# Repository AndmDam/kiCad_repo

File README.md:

# kiCad_repo

Repositorio de mis archivos de mis proyectos de kicad.

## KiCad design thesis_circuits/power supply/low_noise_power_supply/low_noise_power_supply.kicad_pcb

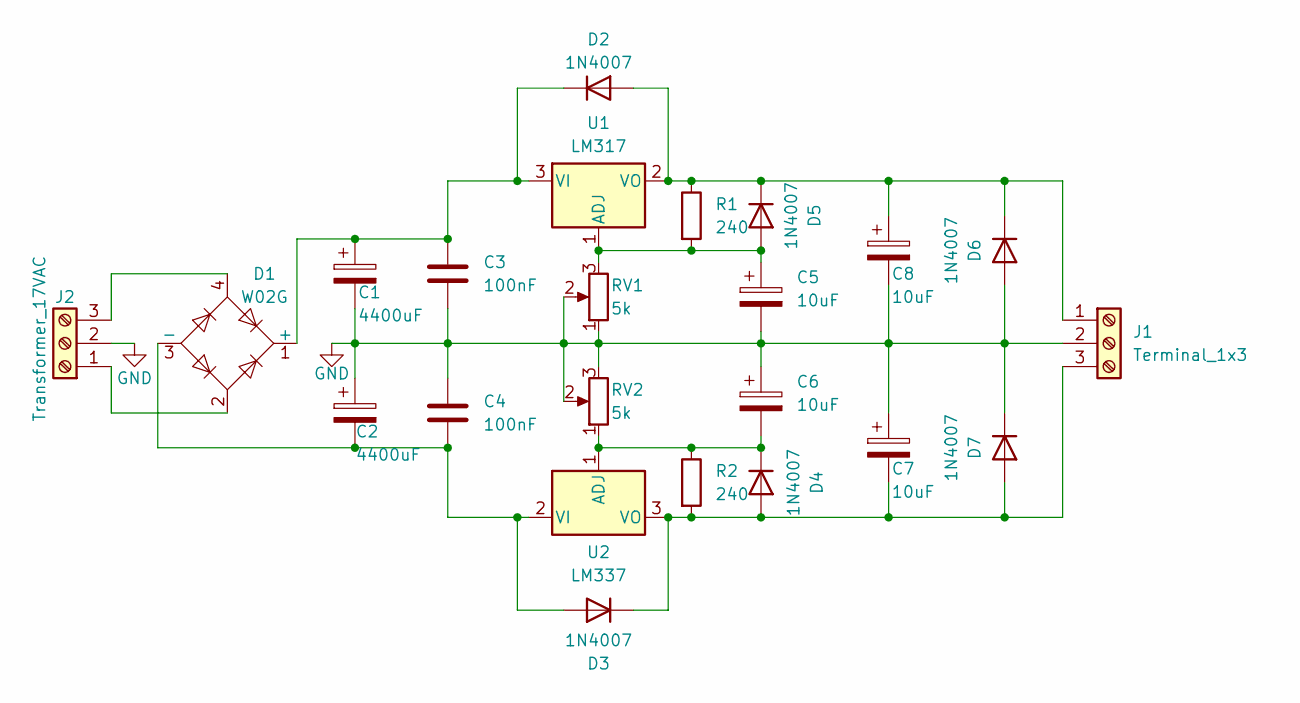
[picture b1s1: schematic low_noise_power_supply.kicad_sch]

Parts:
C1, C2: 4400uF; C_Radial_D18.0mm_H35.5mm_P7.50mm
C3, C4: 100nF; C_Disc_D5.0mm_W2.5mm_P2.50mm
C5, C6, C7, C8: 10uF; CP_Radial_D5.0mm_P2.50mm
D1: W02G; Diode_Bridge_Round_D9.8mm
D2, D3, D4, D5, D6, D7: 1N4007; D_DO-41_SOD81_P10.16mm_Horizontal
J1: Terminal_1x3; PhoenixContact_GMSTBA_2,5_3-G-7,62_1x03_P7.62mm_Horizontal
J2: Transformer_17VAC; PhoenixContact_GMSTBA_2,5_3-G-7,62_1x03_P7.62mm_Horizontal
R1, R2: 240; R_Axial_DIN0204_L3.6mm_D1.6mm_P5.08mm_Horizontal
RV1, RV2: 5k; Potentiometer_Bourns_3299W_Vertical
U1: LM317; TO-220-3_Vertical
U2: LM337; TO-220-3_Vertical

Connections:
GND: C1.2, C2.1, C3.2, C4.1, C5.2, C6.1, C7.1, C8.2, D6.2 (A), D7.1 (K), J1.2, J2.2, RV1.1, RV1.2, RV2.2, RV2.3
unnamed: C1.1, C3.1, D1.1 (+), D2.1 (K), U1.3 (VI)
unnamed: C2.2, C4.2, D1.3 (-), D3.2 (A), U2.2 (VI)
unnamed: C8.1, D2.2 (A), D5.1 (K), D6.1 (K), J1.1, R1.1, U1.2 (VO)
unnamed: C7.2, D3.1 (K), D4.2 (A), D7.2 (A), J1.3, R2.2, U2.3 (VO)
unnamed: C6.2, D4.1 (K), R2.1, RV2.1, U2.1 (ADJ)
unnamed: C5.1, D5.2 (A), R1.2, RV1.3, U1.1 (ADJ)
unnamed: D1.2, J2.1
unnamed: D1.4, J2.3

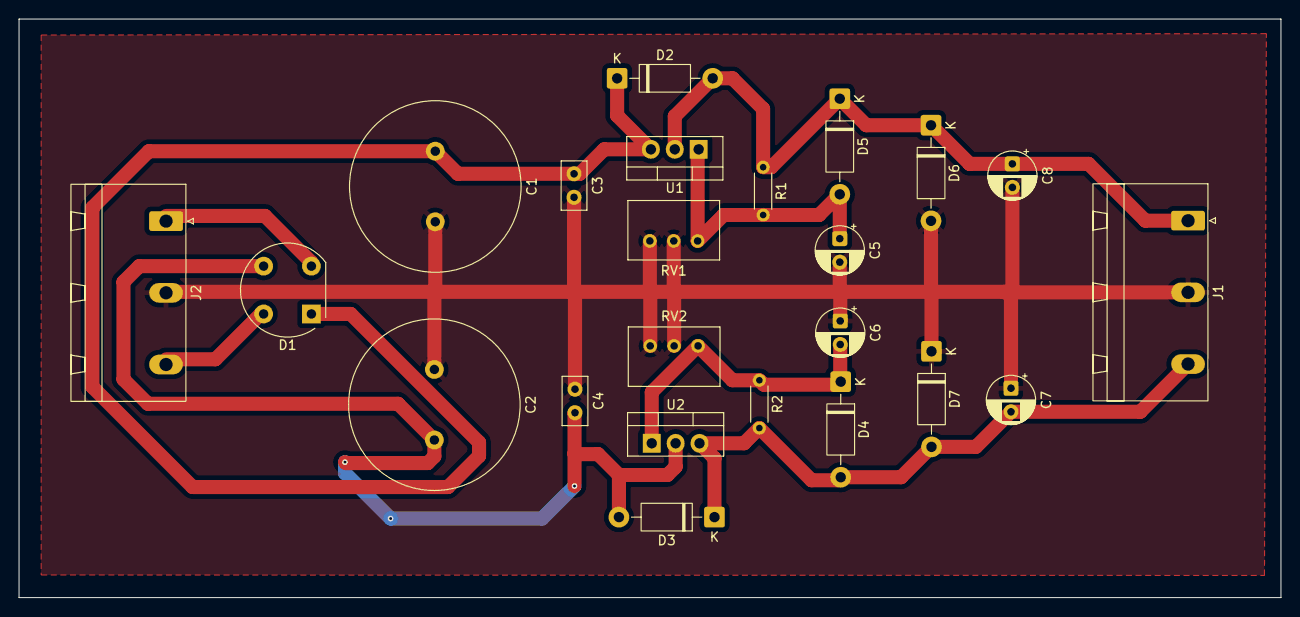
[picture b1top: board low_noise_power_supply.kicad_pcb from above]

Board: 2 copper layers, 134.2 x 61.5 mm, 23 parts (0 on the bottom side), 9 nets.

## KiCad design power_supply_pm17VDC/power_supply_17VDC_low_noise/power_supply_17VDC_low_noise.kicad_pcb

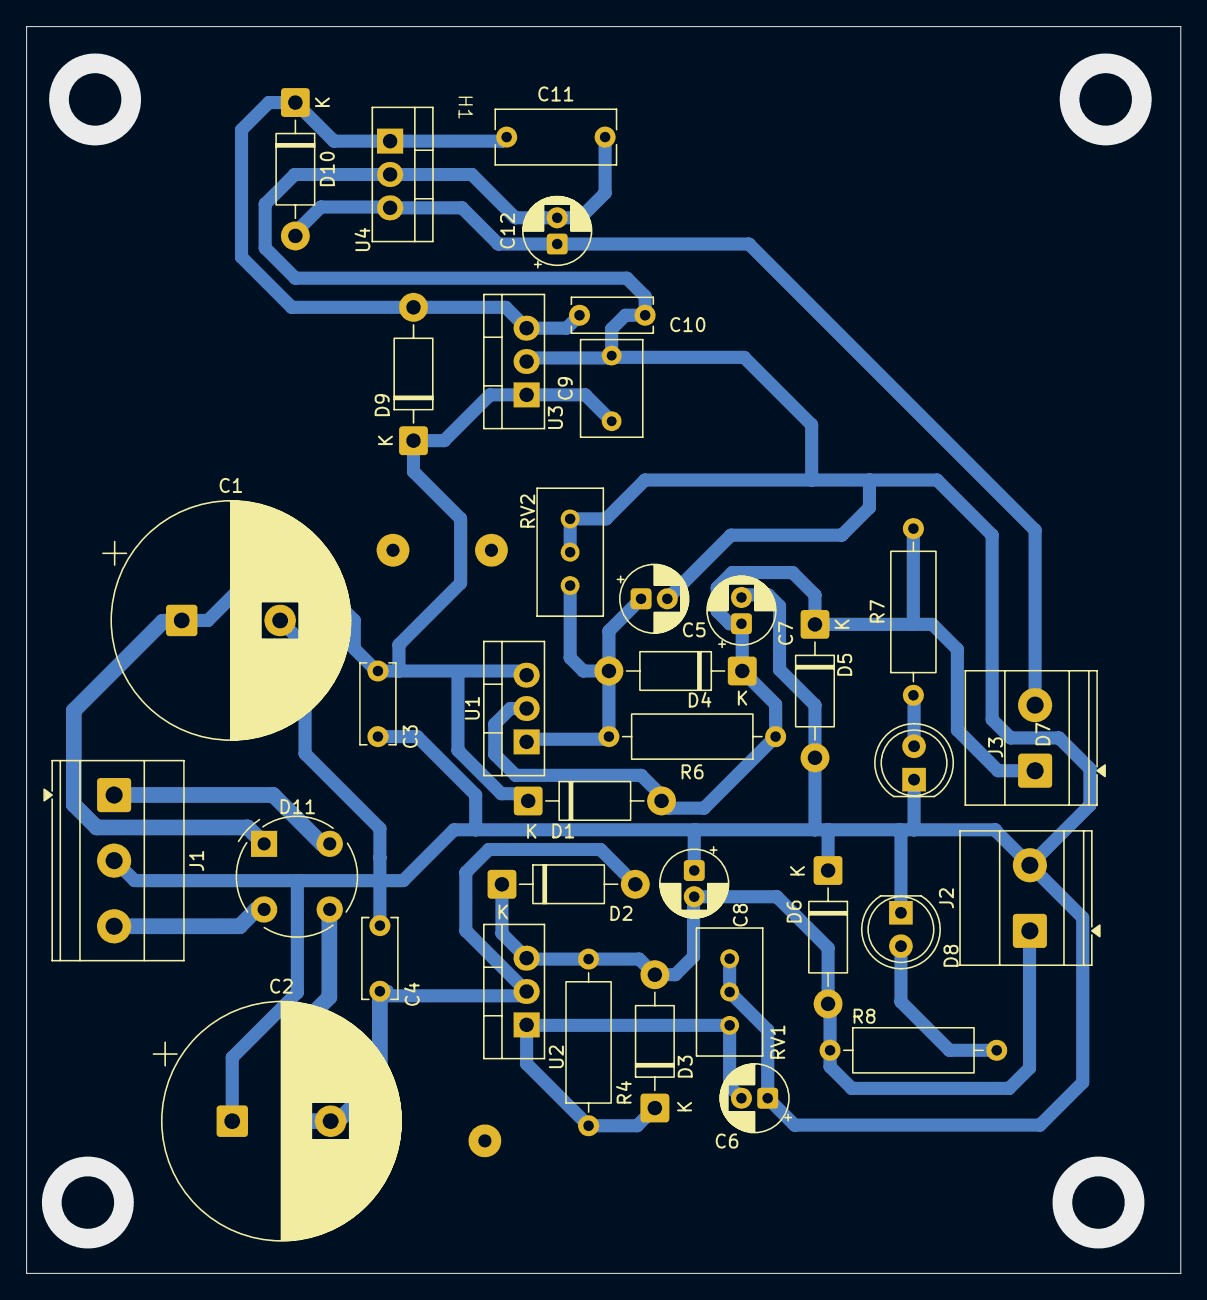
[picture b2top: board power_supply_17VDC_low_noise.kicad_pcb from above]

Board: 2 copper layers, 87.9 x 95.0 mm, 37 parts (0 on the bottom side), 13 nets.

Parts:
C1, C2: 4400uF; CP_Radial_D18.0mm_P7.50mm
C3, C4: 100nF; C_Disc_D6.0mm_W2.5mm_P5.00mm
C5, C6, C7, C8, C12: 10uF; CP_Radial_D5.0mm_P2.00mm
C9: 0.33uF; C_Rect_L7.2mm_W4.5mm_P5.00mm
C10: 10uF; C_Disc_D6.0mm_W2.5mm_P5.00mm
C11: 100nF; C_Rect_L9.0mm_W4.0mm_P7.50mm_MKT
D1, D2, D3, D4, D5, D6, D9, D10: 1N4007; D_DO-41_SOD81_P10.16mm_Horizontal
D7: RED; LED_D5.0mm
D8: LED; LED_D5.0mm
D11: B40R; Diode_Bridge_Round_D9.0mm
H1: Disipador; Dissipator_recycled
J1: Terminal_01x03; TerminalBlock_Phoenix_MKDS-1,5-3_1x03_P5.00mm_Horizontal
J2, J3: Screw_Terminal_01x02; TerminalBlock_Phoenix_MKDS-1,5-2_1x02_P5.00mm_Horizontal
R4, R6: 240; R_Axial_DIN0309_L9.0mm_D3.2mm_P12.70mm_Horizontal
R7, R8: 2k; R_Axial_DIN0309_L9.0mm_D3.2mm_P12.70mm_Horizontal
RV1, RV2: 5k; Potentiometer_Bourns_3296W_Vertical
U1: LM317; TO-220-3_Vertical
U2: LM337; TO-220-3_Vertical
U3: LM7812; TO-220-3_Vertical
U4: LM7805; TO-220-3_Vertical

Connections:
GND: C1.2, C2.1, C3.2, C4.1, C5.2, C6.1, C7.2, C8.1, C9.2, C10.2, C11.2, C12.2, D5.2 (A), D6.1 (K), D7.1 (K), D8.1 (K), J1.2, J2.2, RV1.2, RV1.3, RV2.1, RV2.2, U3.2 (GND), U4.2 (GND)
unnamed: C7.1, D1.2 (A), D4.1 (K), D5.1 (K), J3.1, R6.1, R7.2, U1.2 (VO)
unnamed: C1.1, C3.1, C9.1, D1.1 (K), D9.1 (K), D11.1 (+), U1.3 (VI), U3.1 (VI)
unnamed: C8.2, D2.1 (K), D3.2 (A), D6.2 (A), J2.1, R4.2, R8.1, U2.3 (VO)
unnamed: C6.2, D3.1 (K), R4.1, RV1.1, U2.1 (ADJ)
unnamed: C5.1, D4.2 (A), R6.2, RV2.3, U1.1 (ADJ)
unnamed: D7.2 (A), R7.1
unnamed: D8.2 (A), R8.2
unnamed: C12.1, D10.2 (A), J3.2, U4.3 (VO)
unnamed: C10.1, C11.1, D9.2 (A), D10.1 (K), U3.3 (VO), U4.1 (VI)
unnamed: C2.2, C4.2, D2.2 (A), D11.3 (-), U2.2 (VI)
unnamed: D11.4, J1.1
unnamed: D11.2, J1.3

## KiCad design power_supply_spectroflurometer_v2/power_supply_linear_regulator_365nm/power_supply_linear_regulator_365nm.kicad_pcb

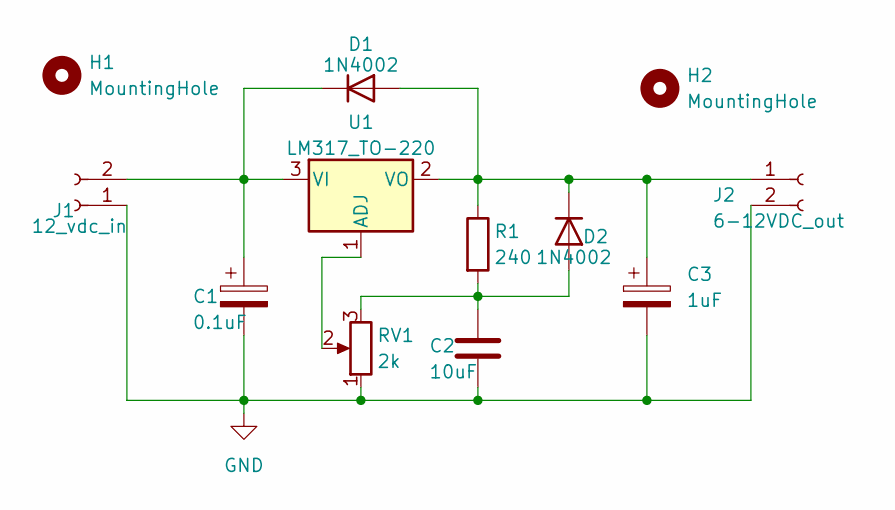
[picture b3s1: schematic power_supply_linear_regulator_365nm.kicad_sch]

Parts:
C1: 0.1uF; C_Radial_D4.0mm_H7.0mm_P1.50mm
C2: 10uF; C_Disc_D5.0mm_W2.5mm_P2.50mm
C3: 1uF; C_Radial_D5.0mm_H11.0mm_P2.00mm
D1, D2: 1N4002; D_DO-41_SOD81_P10.16mm_Horizontal
H1, H2: MountingHole; MountingHole_3.2mm_M3
J1: 12_vdc_in; Altech_AK100_1x02_P5.00mm
J2: 6-12VDC_out; Altech_AK100_1x02_P5.00mm
R1: 240; R_Axial_DIN0309_L9.0mm_D3.2mm_P12.70mm_Horizontal
RV1: 2k; Potentiometer_Bourns_PTV09A-1_Single_Vertical
U1: LM317_TO-220; TO-220-3_Vertical

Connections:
GND: C1.2, C2.2, C3.2, J1.1, J2.2, RV1.1
unnamed: C3.1, D1.2 (A), D2.1 (K), J2.1, R1.1, U1.2 (VO)
unnamed: C1.1, D1.1 (K), J1.2, U1.3 (VI)
unnamed: C2.1, D2.2 (A), R1.2, RV1.3
unnamed: RV1.2, U1.1 (ADJ)

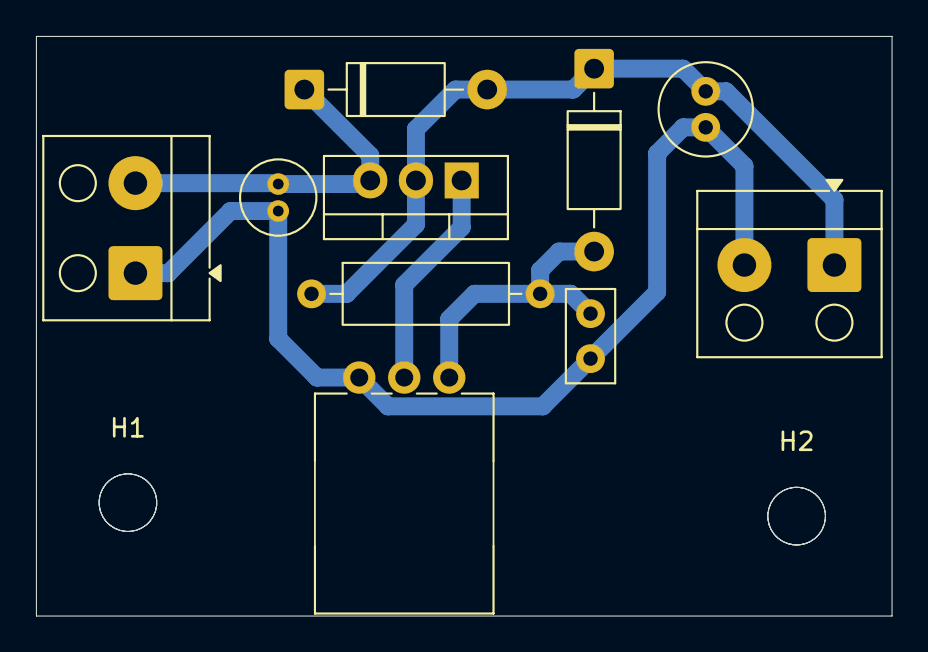
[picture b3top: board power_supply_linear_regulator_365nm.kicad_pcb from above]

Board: 2 copper layers, 47.5 x 32.2 mm, 12 parts (0 on the bottom side), 5 nets.

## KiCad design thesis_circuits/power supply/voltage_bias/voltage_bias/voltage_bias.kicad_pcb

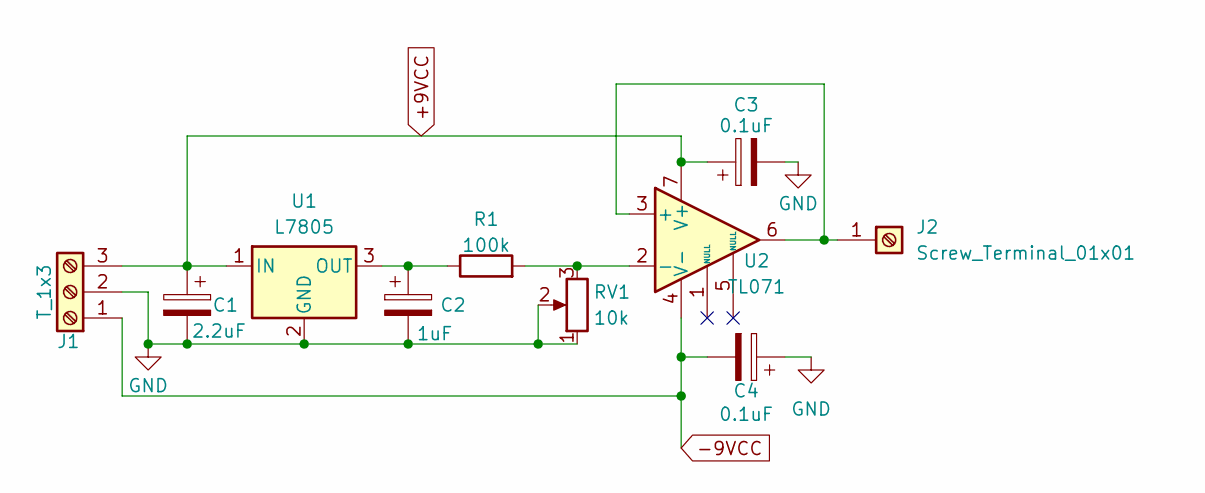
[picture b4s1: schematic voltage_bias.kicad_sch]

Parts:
C1: 2.2uF; C_Radial_D5.0mm_H7.0mm_P2.00mm
C2: 1uF; C_Radial_D5.0mm_H7.0mm_P2.00mm
C3, C4: 0.1uF; C_Radial_D4.0mm_H7.0mm_P1.50mm
J1: T_1x3; PhoenixContact_MSTBA_2,5_3-G-5,08_1x03_P5.08mm_Horizontal
J2: Screw_Terminal_01x01; PinHeader_1x01_P1.00mm_Horizontal
R1: 100k; R_Axial_DIN0207_L6.3mm_D2.5mm_P5.08mm_Vertical
RV1: 10k; Potentiometer_Bourns_3266Y_Vertical
U1: L7805; SIPAK_Vertical
U2: TL071; DIP-8_W7.62mm

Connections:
+9VCC: C1.1, C3.1, J1.3, U1.1 (IN), U2.7 (V+)
-9VCC: C4.2, J1.1, U2.4 (V-)
GND: C1.2, C2.2, C3.2, C4.1, J1.2, RV1.1, RV1.2, U1.2 (GND)
unnamed: J2.1, U2.3 (+), U2.6
unnamed: C2.1, R1.1, U1.3 (OUT)
unnamed: R1.2, RV1.3, U2.2 (-)

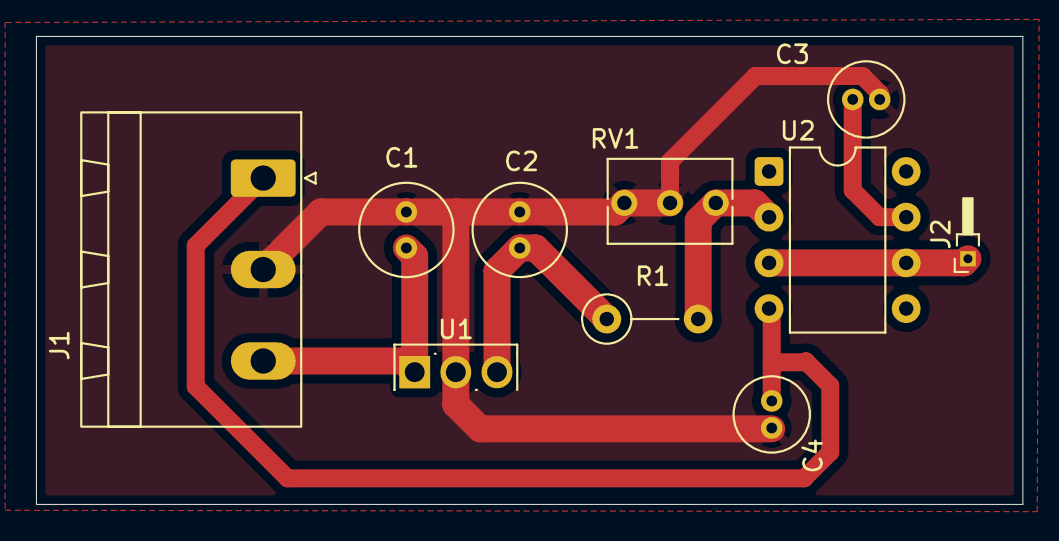
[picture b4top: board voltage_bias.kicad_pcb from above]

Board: 2 copper layers, 54.8 x 26.0 mm, 10 parts (0 on the bottom side), 6 nets.

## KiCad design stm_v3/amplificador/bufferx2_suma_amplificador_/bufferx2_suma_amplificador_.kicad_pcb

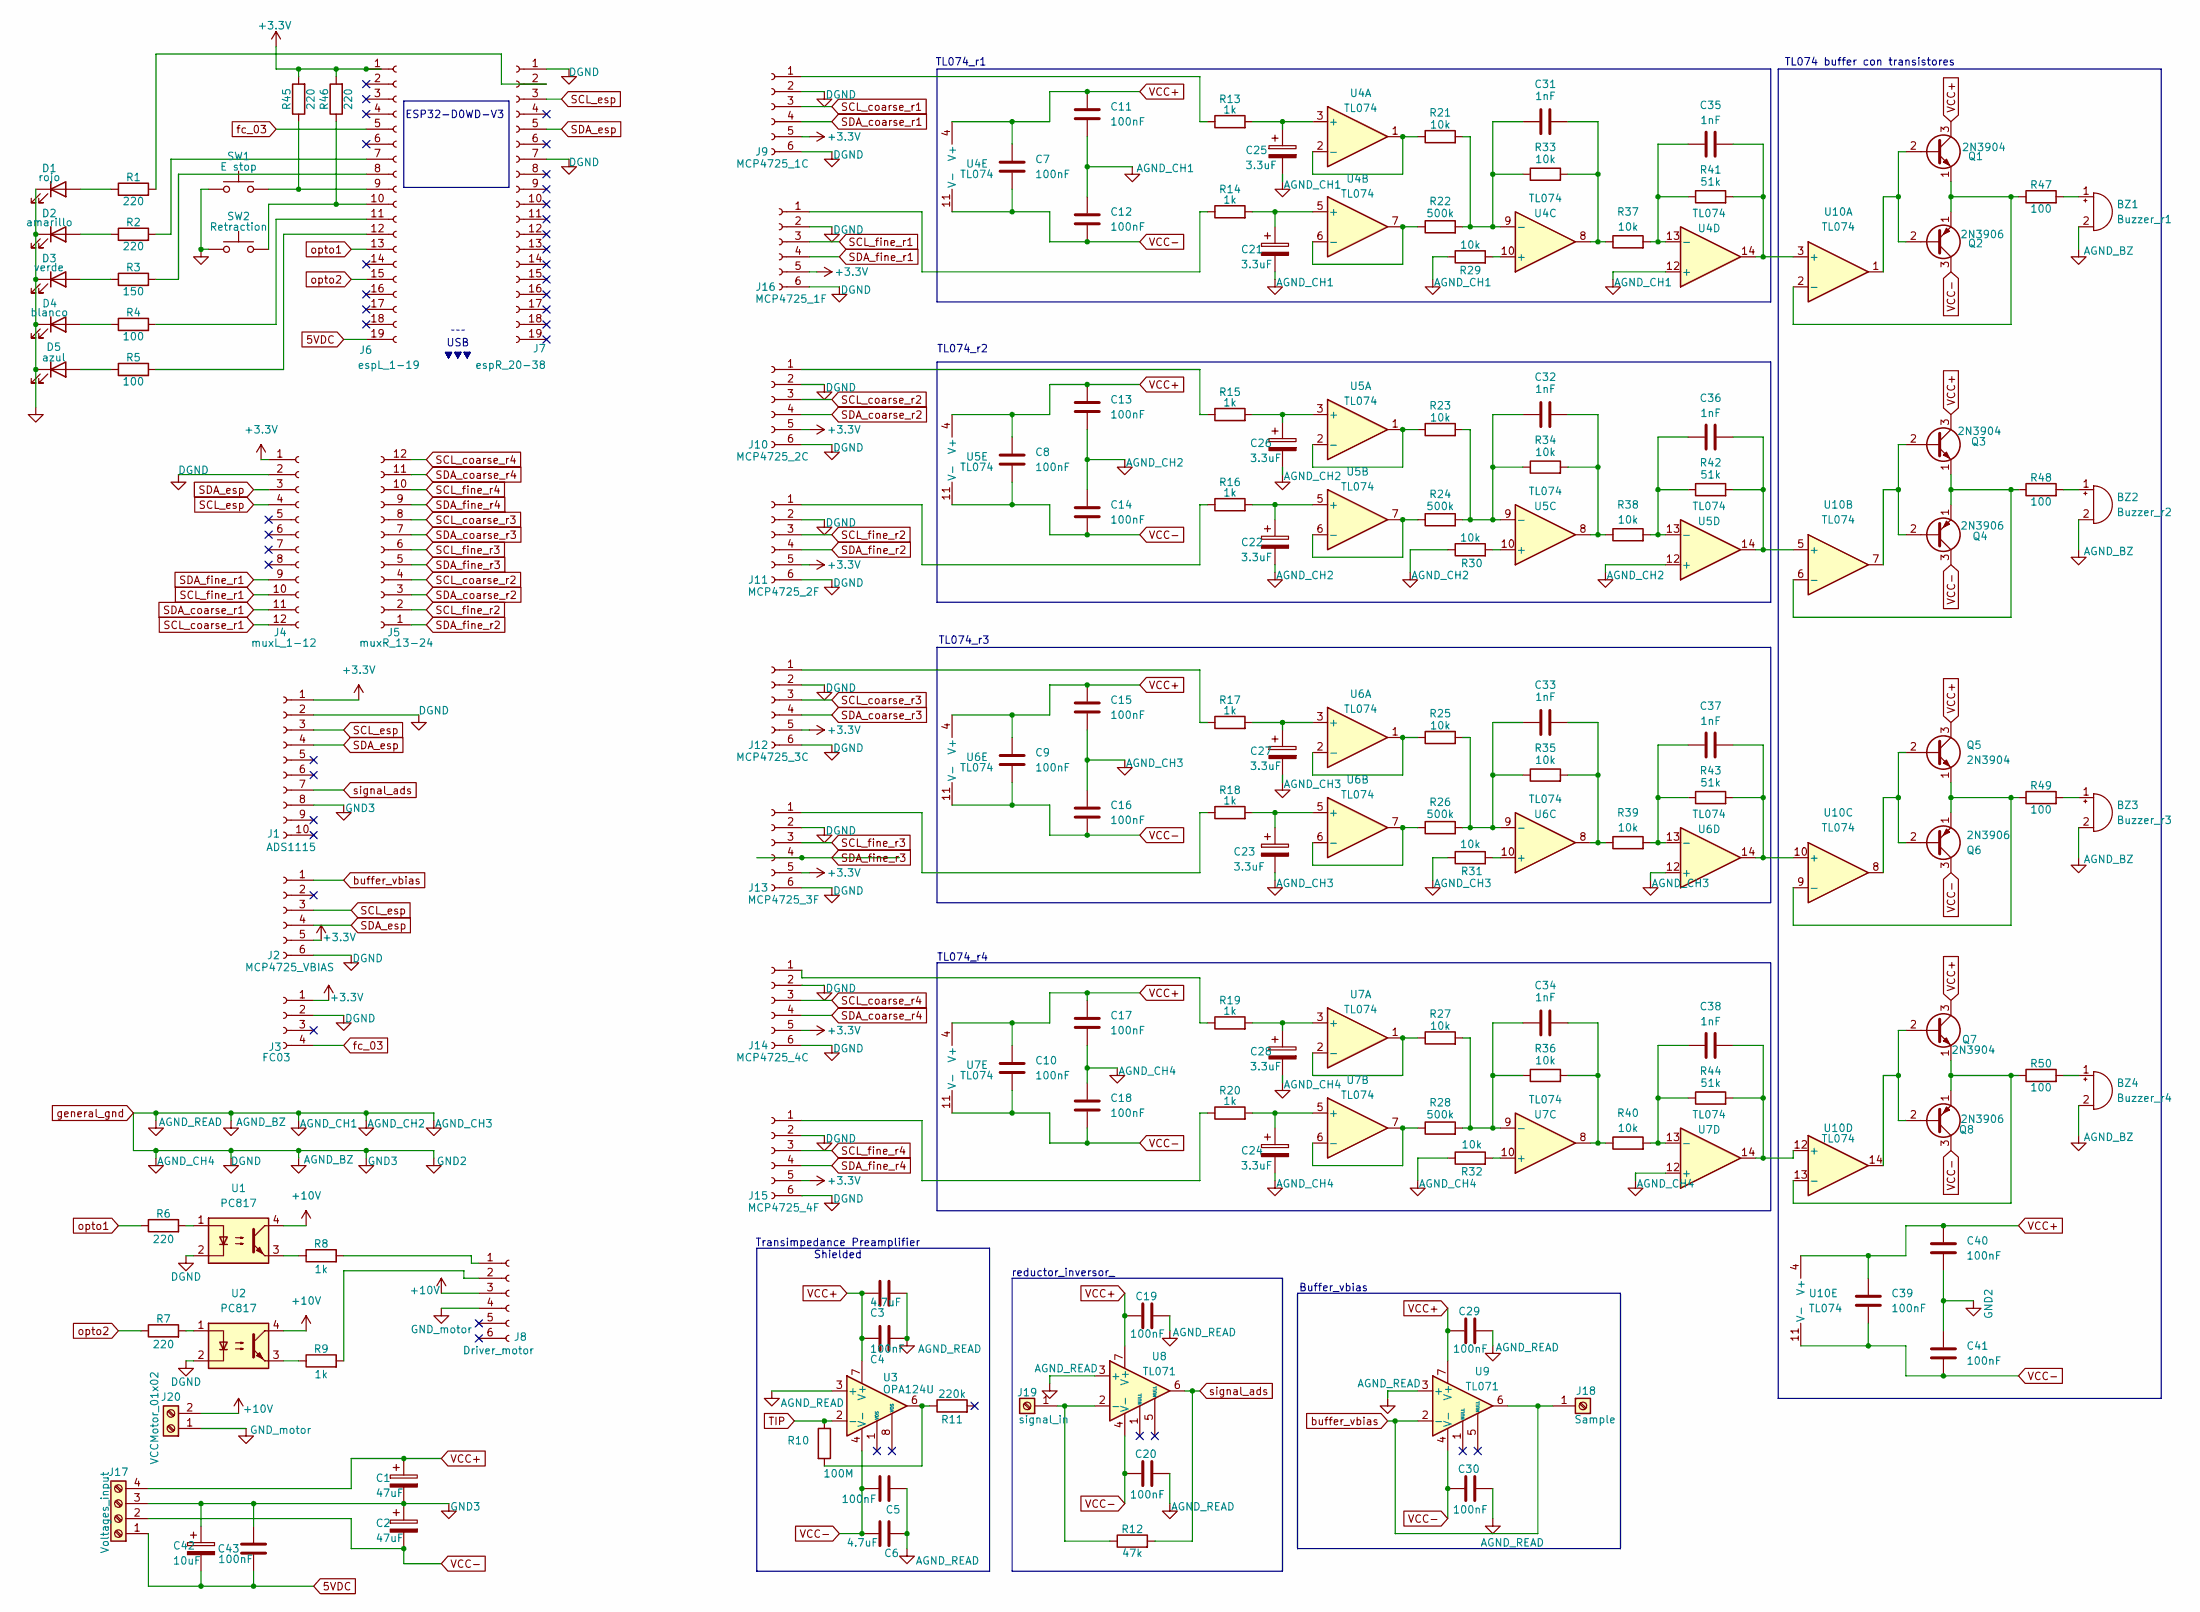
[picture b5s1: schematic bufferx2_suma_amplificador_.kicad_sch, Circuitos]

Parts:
BZ1: Buzzer_r1; SolderWire-0.15sqmm_1x02_P4mm_D0.5mm_OD1.5mm_Relief
BZ2: Buzzer_r2; SolderWire-0.15sqmm_1x02_P4mm_D0.5mm_OD1.5mm_Relief
BZ3: Buzzer_r3; SolderWire-0.15sqmm_1x02_P4mm_D0.5mm_OD1.5mm_Relief
BZ4: Buzzer_r4; SolderWire-0.15sqmm_1x02_P4mm_D0.5mm_OD1.5mm_Relief
C1, C2: 47uF; CP_Radial_D5.0mm_P2.00mm
C3: 4.7uF; CERDIP-14_W7.62mm_SideBrazed_Socket
C4, C5: 100nF
C6: 4.7uF
C7, C8, C9, C10: 100nF; C_Disc_D6.0mm_W2.5mm_P5.00mm
C11, C12, C13, C14, C15, C16, C17, C18, C19, C20, C29, C30, C39, C40, C41: 100nF; C_Disc_D5.0mm_W2.5mm_P2.50mm
C21, C22, C23, C24, C25, C26, C27, C28: 3.3uF; CP_Radial_D5.0mm_P2.00mm
C31, C32, C33, C34, C35, C36, C37, C38: 1nF; C_Disc_D3.0mm_W1.6mm_P2.50mm
C42: 10uF; CP_Radial_D5.0mm_P2.00mm
C43: 100nF; C_Rect_L9.0mm_W3.6mm_P7.50mm_MKT
D1: rojo; LED_D5.0mm
D2: amarillo; LED_D5.0mm
D3: verde; LED_D5.0mm
D4: blanco; LED_D5.0mm
D5: azul; LED_D5.0mm
J1: ADS1115; PinSocket_1x10_P2.54mm_Vertical
J2: MCP4725_VBIAS; PinSocket_1x06_P2.54mm_Vertical
J3: FC03; PinSocket_1x04_P2.54mm_Vertical
J4: muxL_1-12; PinSocket_1x12_P2.54mm_Vertical
J5: muxR_13-24; PinSocket_1x12_P2.54mm_Vertical
J6: espL_1-19; PinSocket_1x19_P2.54mm_Vertical
J7: espR_20-38; PinSocket_1x19_P2.54mm_Vertical
J8: Driver_motor; PinSocket_1x06_P2.54mm_Vertical
J9: MCP4725_1C; PinSocket_1x06_P2.54mm_Vertical
J10: MCP4725_2C; PinSocket_1x06_P2.54mm_Vertical
J11: MCP4725_2F; PinSocket_1x06_P2.54mm_Vertical
J12: MCP4725_3C; PinSocket_1x06_P2.54mm_Vertical
J13: MCP4725_3F; PinSocket_1x06_P2.54mm_Vertical
J14: MCP4725_4C; PinSocket_1x06_P2.54mm_Vertical
J15: MCP4725_4F; PinSocket_1x06_P2.54mm_Vertical
J16: MCP4725_1F; PinSocket_1x06_P2.54mm_Vertical
J17: Voltages_input; TerminalBlock_MaiXu_MX126-5.0-04P_1x04_P5.00mm
J18: Sample; SolderWire-0.1sqmm_1x01_D0.4mm_OD1mm_Relief
J19: signal_in; SolderWire-0.1sqmm_1x01_D0.4mm_OD1mm_Relief
J20: VCCMotor_01x02; TerminalBlock_MaiXu_MX126-5.0-02P_1x02_P5.00mm
Q1, Q3, Q5, Q7: 2N3904; TO-92_Inline
Q2, Q4, Q6, Q8: 2N3906; TO-92_Inline
R1, R2, R6, R7, R45, R46: 220; R_Axial_DIN0309_L9.0mm_D3.2mm_P12.70mm_Horizontal
R3: 150; R_Axial_DIN0309_L9.0mm_D3.2mm_P12.70mm_Horizontal
R4, R5, R47, R48, R49, R50: 100; R_Axial_DIN0309_L9.0mm_D3.2mm_P12.70mm_Horizontal
R8, R9, R13, R14, R15, R16, R17, R18, R19, R20: 1k; R_Axial_DIN0309_L9.0mm_D3.2mm_P12.70mm_Horizontal
R10: 100M; R_Axial_DIN0309_L9.0mm_D3.2mm_P12.70mm_Horizontal
R11: 220k; R_Axial_DIN0309_L9.0mm_D3.2mm_P12.70mm_Horizontal
R12: 47k; R_Axial_DIN0309_L9.0mm_D3.2mm_P12.70mm_Horizontal
R21, R23, R25, R27: 10k; R_Axial_DIN0207_L6.3mm_D2.5mm_P7.62mm_Horizontal
R22, R24, R26, R28: 500k; R_Axial_DIN0309_L9.0mm_D3.2mm_P12.70mm_Horizontal
R29, R30, R31, R32, R33, R34, R35, R36, R37, R38, R39, R40: 10k; R_Axial_DIN0309_L9.0mm_D3.2mm_P12.70mm_Horizontal
R41, R42, R43, R44: 51k; R_Axial_DIN0309_L9.0mm_D3.2mm_P12.70mm_Horizontal
SW1: E stop; SW_PUSH_6mm_H8mm
SW2: Retraction; SW_PUSH_6mm_H8mm
U1, U2: PC817; DIP-4_W7.62mm
U3: OPA124U
U4, U5, U6, U7, U10: TL074; CERDIP-14_W7.62mm_SideBrazed_Socket
U8, U9: TL071; CERDIP-8_W7.62mm_SideBrazed_Socket

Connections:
5VDC: C42.2, C43.1, J6.19, J17.1
+3.3V: J1.1, J2.5, J3.1, J4.1, J6.1, J9.5, J10.5, J11.5, J12.5, J13.5, J14.5, J15.5, J16.5, R45.2, R46.2
+10V: J8.3, J20.2, U1.4, U2.4
GND_motor: J8.4, J20.1
unnamed: BZ1.1 (+), R47.2
unnamed: BZ2.1 (+), R48.2
unnamed: BZ3.1 (+), R49.2
unnamed: BZ4.1 (+), R50.2
unnamed: C31.2, R33.2, R37.1, U4.8
unnamed: C32.2, R34.2, R38.1, U5.8
unnamed: C33.2, R35.2, R39.1, U6.8
unnamed: C34.2, R36.2, R40.1, U7.8
unnamed: D1.2 (A), R1.1
unnamed: D2.2 (A), R2.1
unnamed: D3.2 (A), R3.1
unnamed: D4.2 (A), R4.1
unnamed: D5.2 (A), R5.1
unnamed: J6.7, R2.2
unnamed: J6.8, R3.2
unnamed: J6.9, R45.1, SW1.1
unnamed: J6.10, R46.1, SW2.1
unnamed: J6.11, R4.2
unnamed: J6.12, R5.2
unnamed: J7.2, R1.2
unnamed: J8.1, R8.2
unnamed: J8.2, R9.2
unnamed: J9.1, R13.1
unnamed: J10.1, R15.1
unnamed: J11.1, R16.1
unnamed: J12.1, R17.1
unnamed: J13.1, R18.1
unnamed: J14.1, R19.1
unnamed: J15.1, R20.1
unnamed: J16.1, R14.1
unnamed: J19.1, R12.1, U8.2 (-)
unnamed: Q1.2 (B), Q2.2 (B), U10.1
unnamed: Q1.1 (E), Q2.1 (E), R47.1, U10.2 (-)
unnamed: Q3.2 (B), Q4.2 (B), U10.7
unnamed: Q3.1 (E), Q4.1 (E), R48.1, U10.6 (-)
unnamed: Q5.2 (B), Q6.2 (B), U10.8
unnamed: Q5.1 (E), Q6.1 (E), R49.1, U10.9 (-)
unnamed: Q7.2 (B), Q8.2 (B), U10.14
unnamed: Q7.1 (E), Q8.1 (E), R50.1, U10.13 (-)
unnamed: R6.2, U1.1
unnamed: R7.2, U2.1
unnamed: R8.1, U1.3
unnamed: R9.1, U2.3
unnamed: R10.1, U3.2 (-)
unnamed: R10.2, R11.1, U3.6
unnamed: C25.1, R13.2, U4.3 (+)
unnamed: R21.1, U4.1, U4.2 (-)
unnamed: C21.1, R14.2, U4.5 (+)
unnamed: R22.1, U4.6 (-), U4.7
unnamed: R29.2, U4.10 (+)
unnamed: C31.1, R21.2, R22.2, R33.1, U4.9 (-)
unnamed: C35.1, R37.2, R41.1, U4.13 (-)
unnamed: C26.1, R15.2, U5.3 (+)
unnamed: R23.1, U5.1, U5.2 (-)
unnamed: C22.1, R16.2, U5.5 (+)
unnamed: R24.1, U5.6 (-), U5.7
unnamed: R30.2, U5.10 (+)
unnamed: C32.1, R23.2, R24.2, R34.1, U5.9 (-)
unnamed: C36.1, R38.2, R42.1, U5.13 (-)
unnamed: C27.1, R17.2, U6.3 (+)
unnamed: R25.1, U6.1, U6.2 (-)
unnamed: C23.1, R18.2, U6.5 (+)
unnamed: R26.1, U6.6 (-), U6.7
unnamed: R31.2, U6.10 (+)
unnamed: C33.1, R25.2, R26.2, R35.1, U6.9 (-)
unnamed: C37.1, R39.2, R43.1, U6.13 (-)
unnamed: C28.1, R19.2, U7.3 (+)
unnamed: R27.1, U7.1, U7.2 (-)
unnamed: C24.1, R20.2, U7.5 (+)
unnamed: R28.1, U7.6 (-), U7.7
unnamed: R32.2, U7.10 (+)
unnamed: C34.1, R27.2, R28.2, R36.1, U7.9 (-)
unnamed: C38.1, R40.2, R44.1, U7.13 (-)
unnamed: C35.2, R41.2, U4.14, U10.3 (+)
unnamed: C36.2, R42.2, U5.14, U10.5 (+)
unnamed: C37.2, R43.2, U6.14, U10.10 (+)
unnamed: C38.2, R44.2, U7.14, U10.12 (+)
SCL_coarse_r1: J4.12, J9.3
SCL_coarse_r2: J5.4, J10.3
SCL_coarse_r3: J5.8, J12.3
SCL_coarse_r4: J5.12, J14.3
SCL_esp: J1.3, J2.3, J4.4, J7.3
SCL_fine_r1: J4.10, J16.3
SCL_fine_r2: J5.2, J11.3
SCL_fine_r3: J5.6, J13.3
SCL_fine_r4: J5.10, J15.3
SDA_coarse_r1: J4.11, J9.4
SDA_coarse_r2: J5.3, J10.4
SDA_coarse_r3: J5.7, J12.4
SDA_coarse_r4: J5.11, J14.4
SDA_esp: J1.4, J2.4, J4.3, J7.5
SDA_fine_r1: J4.9, J16.4
SDA_fine_r2: J5.1, J11.4
SDA_fine_r3: J5.5, J13.4
SDA_fine_r4: J5.9, J15.4
VCC+: C1.1, C3.2, C4.2, C7.1, C8.1, C9.1, C10.1, C11.1, C13.1, C15.1, C17.1, C19.1, C29.1, C39.1, C40.1, J17.4, Q1.3 (C), Q3.3 (C), Q5.3 (C), Q7.3 (C), U3.7 (V+), U4.4 (V+), U5.4 (V+), U6.4 (V+), U7.4 (V+), U8.7 (V+), U9.7 (V+), U10.4 (V+)
VCC-: C2.2, C5.1, C6.1, C7.2, C8.2, C9.2, C10.2, C12.2, C14.2, C16.2, C18.2, C20.1, C30.1, C39.2, C41.2, J17.2, Q2.3 (C), Q4.3 (C), Q6.3 (C), Q8.3 (C), U3.4 (V-), U4.11 (V-), U5.11 (V-), U6.11 (V-), U7.11 (V-), U8.4 (V-), U9.4 (V-), U10.11 (V-)
buffer_vbias: J2.1, J18.1, U9.2 (-), U9.6
fc_03: J3.4, J6.5
general_gnd: BZ1.2 (-), BZ2.2 (-), BZ3.2 (-), BZ4.2 (-), C1.2, C2.1, C3.1, C4.1, C5.2, C6.2, C11.2, C12.1, C13.2, C14.1, C15.2, C16.1, C17.2, C18.1, C19.2, C20.2, C21.2, C22.2, C23.2, C24.2, C25.2, C26.2, C27.2, C28.2, C29.2, C30.2, C40.2, C41.1, C42.1, C43.2, D1.1 (K), D2.1 (K), D3.1 (K), D4.1 (K), D5.1 (K), J1.2, J1.8, J2.6, J3.2, J4.2, J7.1, J7.7, J9.2, J9.6, J10.2, J10.6, J11.2, J11.6, J12.2, J12.6, J13.2, J13.6, J14.2, J14.6, J15.2, J15.6, J16.2, J16.6, J17.3, R29.1, R30.1, R31.1, R32.1, SW1.2, SW2.2, U1.2, U2.2, U3.3 (+), U4.12 (+), U5.12 (+), U6.12 (+), U7.12 (+), U8.3 (+), U9.3 (+)
opto1: J6.13, R6.1
opto2: J6.15, R7.1
signal_ads: J1.7, R12.2, U8.6

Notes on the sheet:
TL074_r2
⁃⁃⁃ USB ▼▼▼
Buffer_vbias
TL074_r3
TL074_r1
TL074_r4
TL074 buffer con transistores
reductor_inversor_
ESP32-D0WD-V3
Transimpedance Preamplifier Shielded

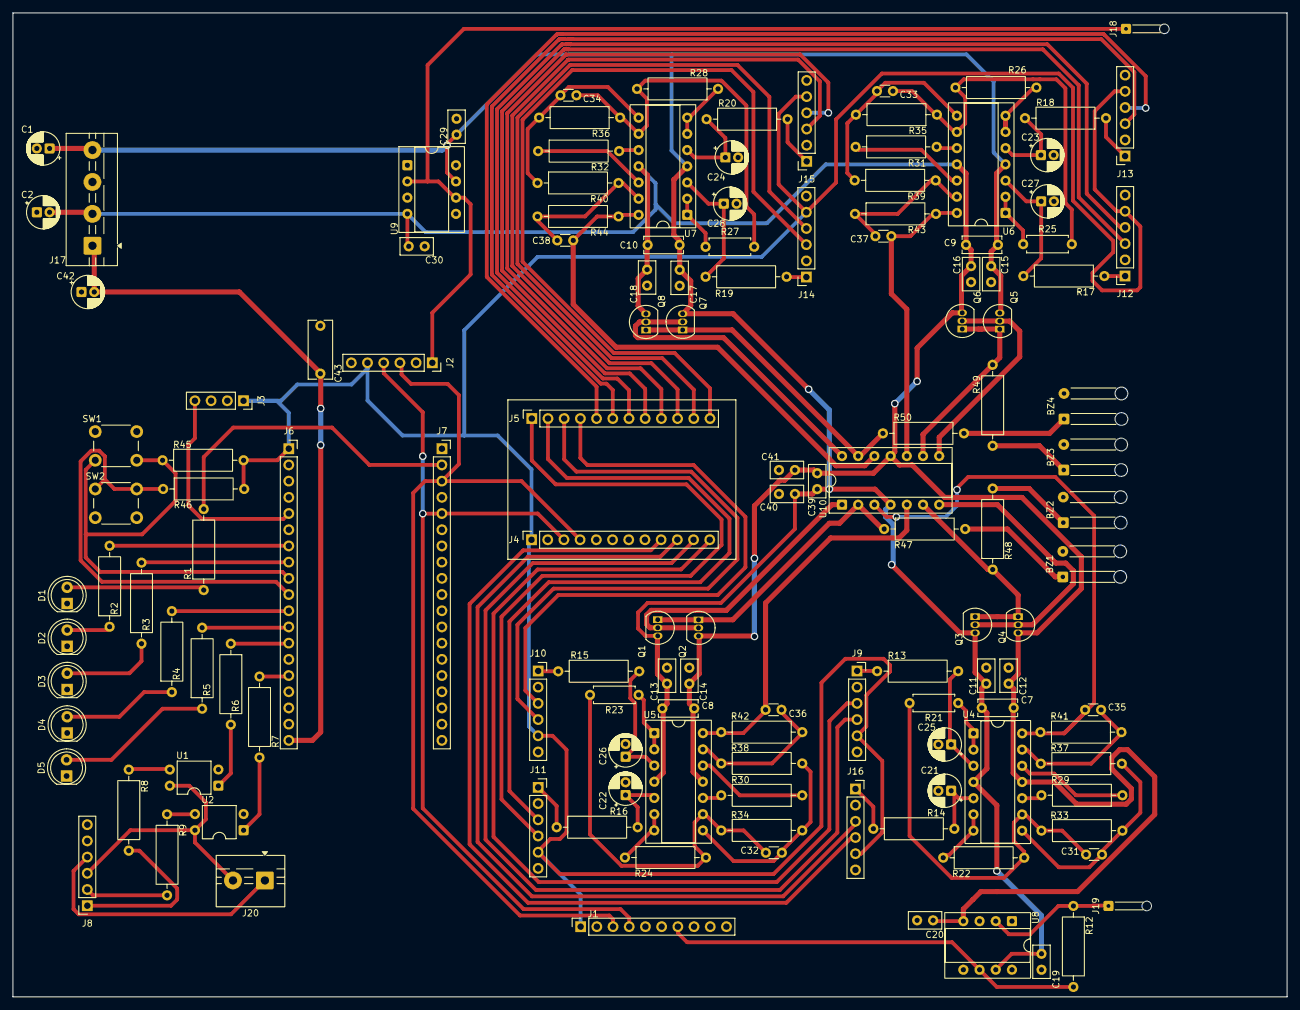
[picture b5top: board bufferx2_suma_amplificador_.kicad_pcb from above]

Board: 2 copper layers, 199.8 x 154.2 mm, 135 parts (0 on the bottom side), 105 nets.

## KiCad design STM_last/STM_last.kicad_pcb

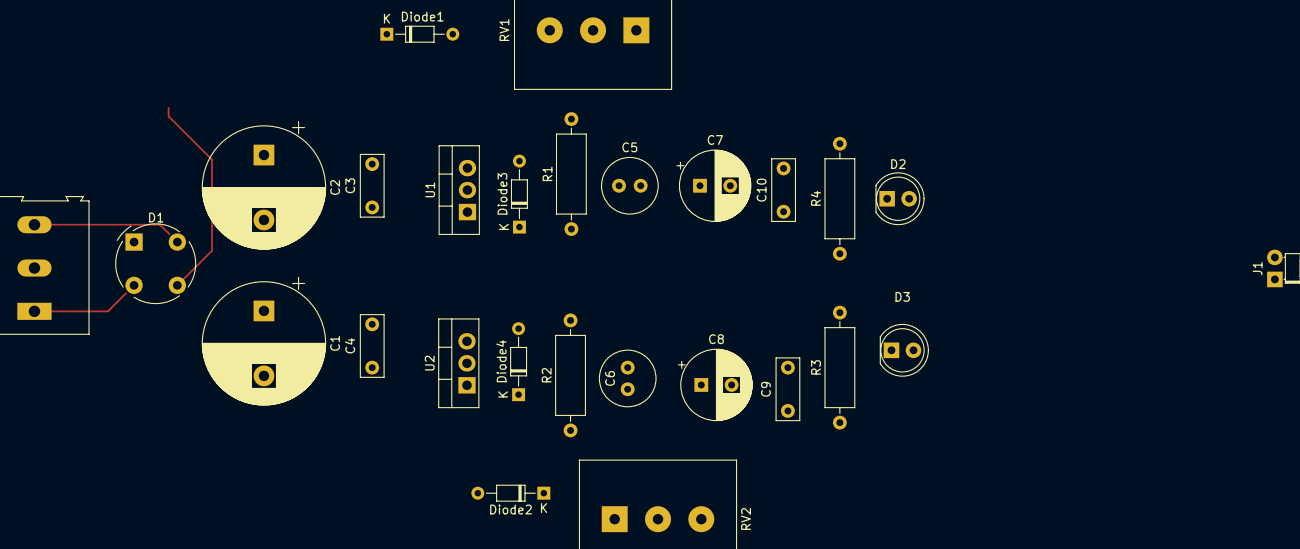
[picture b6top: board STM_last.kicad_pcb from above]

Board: 2 copper layers, 26 parts (0 on the bottom side), 9 nets.

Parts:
C1, C2: 2200uF/25V; CP_Radial_D14.0mm_P7.50mm
C3, C4, C9, C10: 100nF; C_Rect_L7.0mm_W2.5mm_P5.00mm
C5, C6: 10uF; C_Radial_D6.3mm_H5.0mm_P2.50mm
C7, C8: 470uF/25V; CP_Radial_D8.0mm_P3.50mm
D1: 2W10; Diode_Bridge_Round_D9.0mm
D2, D3: LED; LED_D5.0mm
Diode1, Diode2, Diode3, Diode4: 1N4001; D_DO-34_SOD68_P7.62mm_Horizontal
J1: Screw_Terminal_01x03; LED_D1.8mm_W1.8mm_H2.4mm_Horizontal_O1.27mm_Z4.9mm
R1, R2: 200k; R_Axial_DIN0309_L9.0mm_D3.2mm_P12.70mm_Horizontal
R3, R4: 4.7k; R_Axial_DIN0309_L9.0mm_D3.2mm_P12.70mm_Horizontal
RV1, RV2: 2k; Potentiometer_Alps_RK163_Single_Horizontal
U1: LM317; TO-220-3_Vertical
U2: LM337; TO-220-3_Vertical

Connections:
Earth: C1.2, C2.1, C3.2, C4.1, C5.2, C6.1, C7.2, C8.1, C9.2, C10.1, D2.1 (K), D3.1 (K), J1.2, RV1.2, RV1.3, RV2.1, RV2.2
unnamed: C1.1, C3.1, D1.1 (+), Diode1.1 (K), U1.3 (VI)
unnamed: C2.2, C4.2, D1.3 (-), Diode2.2 (A), U2.2 (VI)
unnamed: D2.2 (A), R3.1
unnamed: D3.2 (A), R4.2
unnamed: C7.1, C9.1, Diode1.2 (A), Diode3.1 (K), J1.1, R1.1, R3.2, U1.2 (VO)
unnamed: C8.2, C10.2, Diode2.1 (K), Diode4.2 (A), R2.1, R4.1, U2.3 (VO)
unnamed: C5.1, Diode3.2 (A), R1.2, RV1.1, U1.1 (ADJ)
unnamed: C6.2, Diode4.1 (K), R2.2, RV2.3, U2.1 (ADJ)

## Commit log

2024-10-27 primer commit, tesis Buffer normal.
2024-11-04 añado el archivo que ignora las librerias y actualizo la info de la tesis, están todos los circuitos ya hechos, al menos en esquemático, revisar footprints
2025-03-30 proyecto_smps_artillery, ingeniería a la inversa.
2025-07-03 ultimos modificaciones a fuente
2026-02-14 agregando los repositorios del STM version pro ademas de la fuente de pm17VDC +5V para el ESP32.
2026-02-14 agregando imagenes y pdf
2026-02-17 finalizado STM y fuente de poder limpia, todo conforme a las huellas.
2026-02-23 subiendo repo de STM y de fuente simetrica
2026-02-23 Corrigiendo pcbs de fuente de poder
2026-05-08 chore: aplicar .gitignore y limpiar los archivos temporales de kiCad
